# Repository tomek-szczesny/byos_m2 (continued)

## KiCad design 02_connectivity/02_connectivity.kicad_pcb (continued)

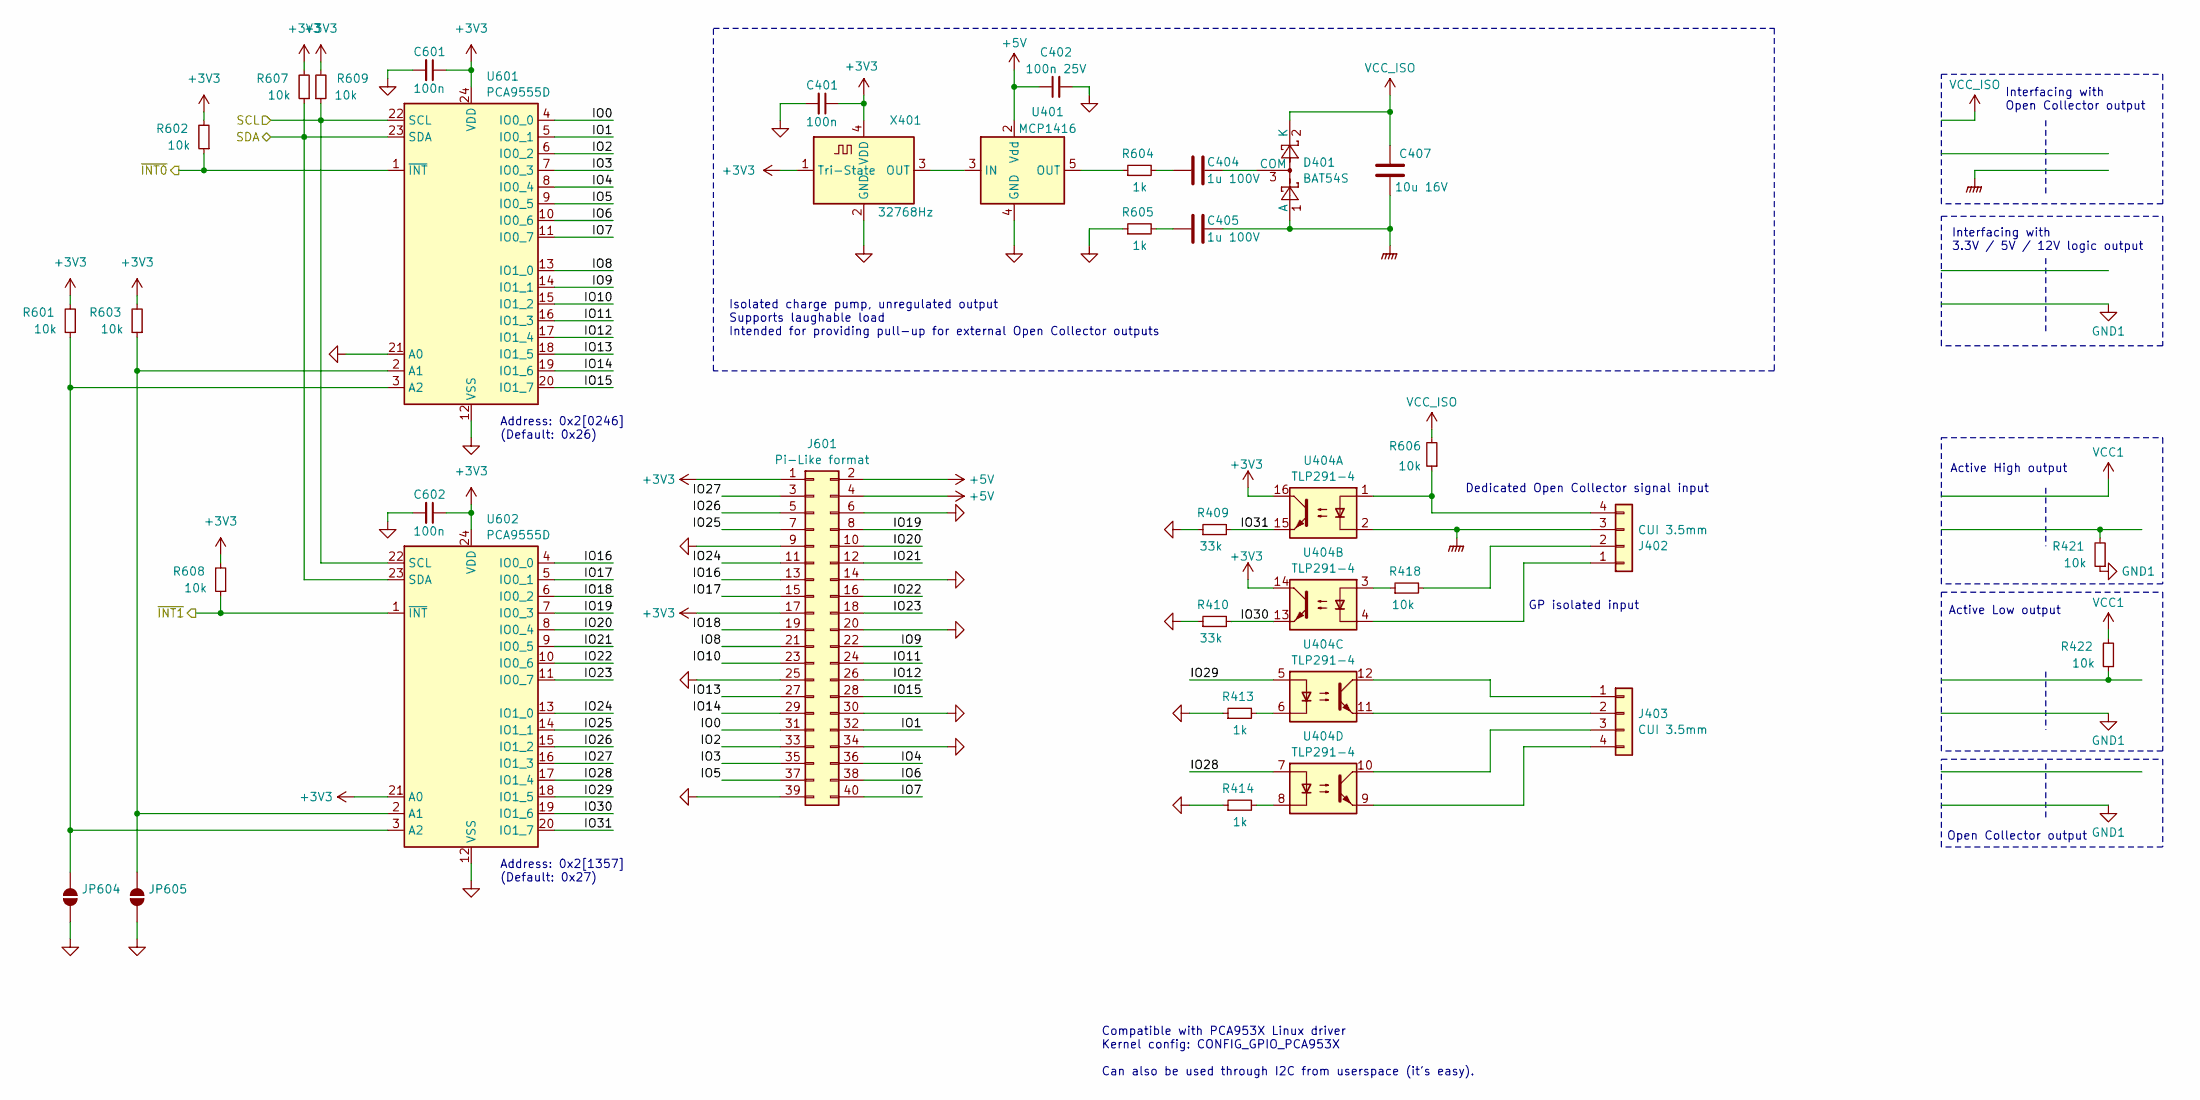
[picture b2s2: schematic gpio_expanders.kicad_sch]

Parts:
C401, C601, C602: 100n; C_0603_1608Metric
C402: 100n 25V; C_0603_1608Metric
C404, C405: 1u 100V; C_1206_3216Metric
C407: 10u 16V; C_1206_3216Metric
D401: BAT54S; SOT-23
J402, J403: CUI 3.5mm; CUI_TBP03R1-350-04BE
J601: Pi-Like format; PinHeader_2x20_P2.54mm_Horizontal
JP604, JP605: SolderJumper_2_Open; SolderJumper-2_P1.3mm_Open_TrianglePad1.0x1.5mm
R409, R410: 33k; R_0603_1608Metric
R413, R414, R604, R605: 1k; R_0603_1608Metric
R418, R421, R422, R601, R602, R603, R606, R607, R608, R609: 10k; R_0603_1608Metric
U401: MCP1416; SOT-23-5
U404: TLP291-4; SOIC-16_4.55x10.3mm_P1.27mm
U601, U602: PCA9555D; SOIC-24W_7.5x15.4mm_P1.27mm
X401: ECS-327MVATX-5-CN-TR; Oscillator_SMD_EuroQuartz_XO53-4Pin_5.0x3.2mm

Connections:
+3V3: C401.1, C601.1, C602.1, J601.1, J601.17, R601.2, R602.2, R603.2, R607.2, R608.2, R609.2, U404.14, U404.16, U601.24 (VDD), U602.21 (A0), U602.24 (VDD), X401.1 (Tri-State), X401.4 (VDD); also elsewhere on the board
+5V: C402.1, J601.2, J601.4, U401.2 (Vdd); also elsewhere on the board
/GPIO1_B2: R608.1, U602.1 (~INT); also elsewhere on the board
/GPIO1_B3: R602.1, U601.1 (~INT); also elsewhere on the board
/GPIO Expanders/IO0: J601.31, U601.4 (IO0_0)
/GPIO Expanders/IO1: J601.32, U601.5 (IO0_1)
/GPIO Expanders/IO2: J601.33, U601.6 (IO0_2)
/GPIO Expanders/IO3: J601.35, U601.7 (IO0_3)
/GPIO Expanders/IO4: J601.36, U601.8 (IO0_4)
/GPIO Expanders/IO5: J601.37, U601.9 (IO0_5)
/GPIO Expanders/IO6: J601.38, U601.10 (IO0_6)
/GPIO Expanders/IO7: J601.40, U601.11 (IO0_7)
/GPIO Expanders/IO8: J601.21, U601.13 (IO1_0)
/GPIO Expanders/IO9: J601.22, U601.14 (IO1_1)
/GPIO Expanders/IO10: J601.23, U601.15 (IO1_2)
/GPIO Expanders/IO11: J601.24, U601.16 (IO1_3)
/GPIO Expanders/IO12: J601.26, U601.17 (IO1_4)
/GPIO Expanders/IO13: J601.27, U601.18 (IO1_5)
/GPIO Expanders/IO14: J601.29, U601.19 (IO1_6)
/GPIO Expanders/IO15: J601.28, U601.20 (IO1_7)
/GPIO Expanders/IO16: J601.13, U602.4 (IO0_0)
/GPIO Expanders/IO17: J601.15, U602.5 (IO0_1)
/GPIO Expanders/IO18: J601.19, U602.6 (IO0_2)
/GPIO Expanders/IO19: J601.8, U602.7 (IO0_3)
/GPIO Expanders/IO20: J601.10, U602.8 (IO0_4)
/GPIO Expanders/IO21: J601.12, U602.9 (IO0_5)
/GPIO Expanders/IO22: J601.16, U602.10 (IO0_6)
/GPIO Expanders/IO23: J601.18, U602.11 (IO0_7)
/GPIO Expanders/IO24: J601.11, U602.13 (IO1_0)
/GPIO Expanders/IO25: J601.7, U602.14 (IO1_1)
/GPIO Expanders/IO26: J601.5, U602.15 (IO1_2)
/GPIO Expanders/IO27: J601.3, U602.16 (IO1_3)
/GPIO Expanders/IO28: U404.7, U602.17 (IO1_4)
/GPIO Expanders/IO29: U404.5, U602.18 (IO1_5)
/GPIO Expanders/IO30: R410.2, U404.13, U602.19 (IO1_6)
/GPIO Expanders/IO31: R409.2, U404.15, U602.20 (IO1_7)
/I2C6_SCL: R609.1, U601.22 (SCL), U602.22 (SCL); also elsewhere on the board
/I2C6_SDA: R607.1, U601.23 (SDA), U602.23 (SDA); also elsewhere on the board
GND: C401.2, C402.2, C601.2, C602.2, J601.6, J601.9, J601.14, J601.20, J601.25, J601.30, J601.34, J601.39, JP604.2 (B), JP605.2 (B), R409.1, R410.1, R413.1, R414.1, R605.1, U401.4 (GND), U601.12 (VSS), U601.21 (A0), U602.12 (VSS), X401.2 (GND); also elsewhere on the board
GND_ISO: C405.1, C407.1, D401.1 (A), J402.3, U404.2
unnamed: C404.2, R604.2
unnamed: C405.2, R605.2
unnamed: C404.1, D401.3 (COM)
unnamed: J402.1, U404.4
unnamed: J402.2, R418.2
unnamed: J402.4, R606.1, U404.1
unnamed: J403.1, U404.12
unnamed: J403.2, U404.11
unnamed: J403.3, U404.10
unnamed: J403.4, U404.9
unnamed: JP604.1 (A), R601.1, U601.3 (A2), U602.3 (A2)
unnamed: JP605.1 (A), R603.1, U601.2 (A1), U602.2 (A1)
unnamed: R413.2, U404.6
unnamed: R414.2, U404.8
unnamed: R418.1, U404.3
unnamed: U401.3 (IN), X401.3 (OUT)
unnamed: R604.1, U401.5 (OUT)
VCC_ISO: C407.2, D401.2 (K), R606.2

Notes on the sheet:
Isolated charge pump, unregulated output Supports laughable load Intended for providing pull-up for external Open Collector outputs
Active High output
Open Collector output
Dedicated Open Collector signal input
Active Low output
Interfacing with Open Collector output
Address: 0x2[1357] (Default: 0x27)
Interfacing with 3.3V / 5V / 12V logic output
GP isolated input
Compatible with PCA953X Linux driver Kernel config: CONFIG_GPIO_PCA953X Can also be used through I2C from userspace (it's easy).
Address: 0x2[0246] (Default: 0x26)

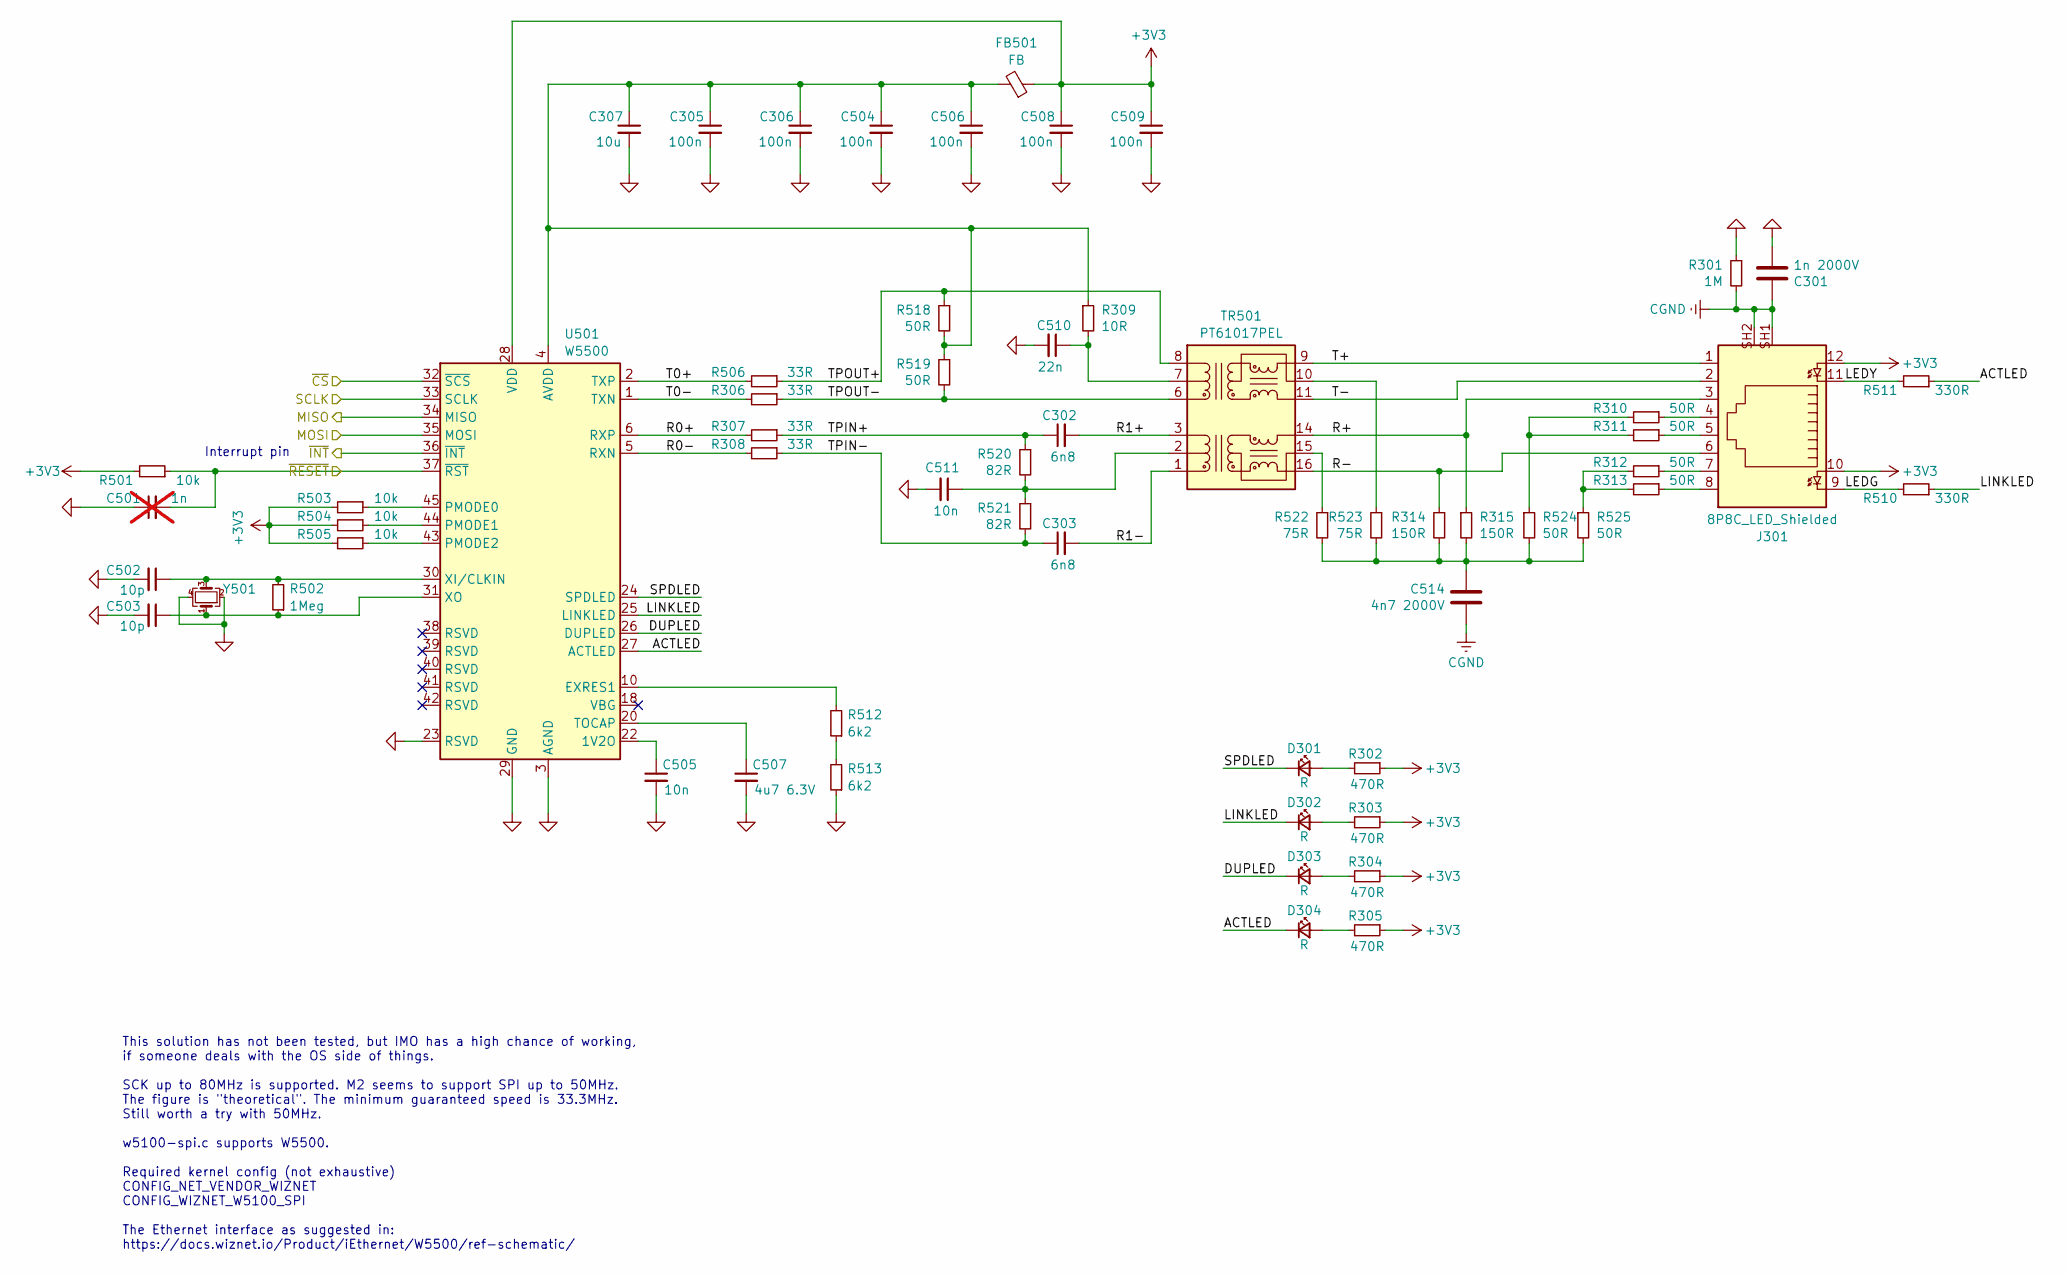
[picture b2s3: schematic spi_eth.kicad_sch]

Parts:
C301: 1n 2000V; C_1206_3216Metric
C302, C303: 6n8; C_0603_1608Metric
C305, C306, C504, C506, C508, C509: 100n; C_0603_1608Metric
C307: 10u; C_0603_1608Metric
C501: 1n; C_0603_1608Metric; not fitted
C502, C503: 10p; C_0603_1608Metric
C505, C511: 10n; C_0603_1608Metric
C507: 4u7 6.3V; C_0603_1608Metric
C510: 22n; C_0603_1608Metric
C514: 4n7 2000V; C_1206_3216Metric
D301, D302, D303, D304: R; LED_0603_1608Metric
FB501: FB; L_0603_1608Metric
J301: 8P8C_LED_Shielded; PHOENIX_1149867
R301: 1M; R_0603_1608Metric
R302, R303, R304, R305: 470R; R_0603_1608Metric
R306, R307, R308, R506: 33R; R_0603_1608Metric
R309: 10R; R_0603_1608Metric
R310, R311, R312, R313, R518, R519, R524, R525: 50R; R_0603_1608Metric
R314, R315: 150R; R_0603_1608Metric
R501, R503, R504, R505: 10k; R_0603_1608Metric
R502: 1Meg; R_0603_1608Metric
R510, R511: 330R; R_0603_1608Metric
R512, R513: 6k2; R_0603_1608Metric
R520, R521: 82R; R_0603_1608Metric
R522, R523: 75R; R_0603_1608Metric
TR501: PT61017PEL; Transformer_Ethernet_Bourns_PT61017PEL
U501: W5500; LQFP-48_7x7mm_P0.5mm
Y501: ABM8-25.000MHZ-B2-T; Crystal_SMD_3225-4Pin_3.2x2.5mm

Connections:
+3V3: C508.1, C509.1, FB501.1, J301.10, J301.12, R302.1, R303.1, R304.1, R305.1, R501.2, R503.2, R504.2, R505.2, U501.28 (VDD); also elsewhere on the board
/GPIO3_D5: U501.36 (~INT); also elsewhere on the board
/GPIO4_B3: C501.2, R501.1, U501.37 (~RST); also elsewhere on the board
/SPI3_CS0: U501.32 (~SCS); also elsewhere on the board
/SPI3_MISO: U501.34 (MISO); also elsewhere on the board
/SPI3_MOSI: U501.35 (MOSI); also elsewhere on the board
/SPI3_SCK: U501.33 (SCLK); also elsewhere on the board
/SPI Ethernet/ACTLED: D304.1 (K), R511.1, U501.27 (ACTLED)
/SPI Ethernet/DUPLED: D303.1 (K), U501.26 (DUPLED)
/SPI Ethernet/LEDG: J301.9, R510.2
/SPI Ethernet/LEDY: J301.11, R511.2
/SPI Ethernet/LINKLED: D302.1 (K), R510.1, U501.25 (LINKLED)
/SPI Ethernet/R0+: R307.2, U501.6 (RXP)
/SPI Ethernet/R0-: R308.2, U501.5 (RXN)
/SPI Ethernet/R1+: C302.2, TR501.3 (TD-)
/SPI Ethernet/R1-: C303.2, TR501.1 (TD+)
/SPI Ethernet/R+: J301.3, R315.1, TR501.14 (TX-)
/SPI Ethernet/R-: J301.6, R314.1, TR501.16 (TX+)
/SPI Ethernet/SPDLED: D301.1 (K), U501.24 (SPDLED)
/SPI Ethernet/T0+: R506.2, U501.2 (TXP)
/SPI Ethernet/T0-: R306.2, U501.1 (TXN)
/SPI Ethernet/T+: J301.1, TR501.9 (RX-)
/SPI Ethernet/T-: J301.2, TR501.11 (RX+)
/SPI Ethernet/TPIN+: C302.1, R307.1, R520.1
/SPI Ethernet/TPIN-: C303.1, R308.1, R521.2
/SPI Ethernet/TPOUT+: R506.1, R518.1, TR501.8 (RD-)
/SPI Ethernet/TPOUT-: R306.1, R519.2, TR501.6 (RD+)
CGND: C301.1, C514.2, J301.SH1, J301.SH2, R301.2
GND: C301.2, C305.2, C306.2, C307.2, C501.1, C502.2, C503.2, C504.2, C505.2, C506.2, C507.2, C508.2, C509.2, C510.2, C511.2, R301.1, R513.1, U501.3 (AGND), U501.9 (AGND), U501.14 (AGND), U501.16 (AGND), U501.19 (AGND), U501.23 (RSVD), U501.29 (GND), U501.48 (AGND), Y501.2, Y501.4; also elsewhere on the board
unnamed: C305.1, C306.1, C307.1, C504.1, C506.1, FB501.2, R309.1, R518.2, R519.1, U501.4 (AVDD), U501.8 (AVDD), U501.11 (AVDD), U501.15 (AVDD), U501.17 (AVDD), U501.21 (AVDD)
unnamed: C514.1, R314.2, R315.2, R522.2, R523.2, R524.2, R525.2
unnamed: D301.2 (A), R302.2
unnamed: D302.2 (A), R303.2
unnamed: D303.2 (A), R304.2
unnamed: D304.2 (A), R305.2
unnamed: J301.4, R310.1
unnamed: J301.5, R311.1
unnamed: J301.7, R312.1
unnamed: J301.8, R313.1
unnamed: R310.2, R311.2, R524.1
unnamed: R312.2, R313.2, R525.1
unnamed: R512.1, R513.2
unnamed: C510.1, R309.2, TR501.7 (C_RD)
unnamed: R523.1, TR501.10 (C_RX)
unnamed: C511.1, R520.2, R521.1, TR501.2 (C_TD)
unnamed: R522.1, TR501.15 (C_TX)
unnamed: C505.1, U501.22 (1V2O)
unnamed: R512.2, U501.10 (EXRES1)
unnamed: R503.1, U501.45 (PMODE0)
unnamed: R504.1, U501.44 (PMODE1)
unnamed: R505.1, U501.43 (PMODE2)
unnamed: C507.1, U501.20 (TOCAP)
unnamed: C502.1, R502.2, U501.30 (XI/CLKIN), Y501.3
unnamed: C503.1, R502.1, U501.31 (XO), Y501.1

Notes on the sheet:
This solution has not been tested, but IMO has a high chance of working, if someone deals with the OS side of things. SCK up to 80MHz is supported. M2 seems to support SPI up to 50MHz. The figure is "theoretical". The minimum guaranteed speed is 33.3MHz. Still worth a try with 50MHz. w5100-spi.c su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
Interrupt pin

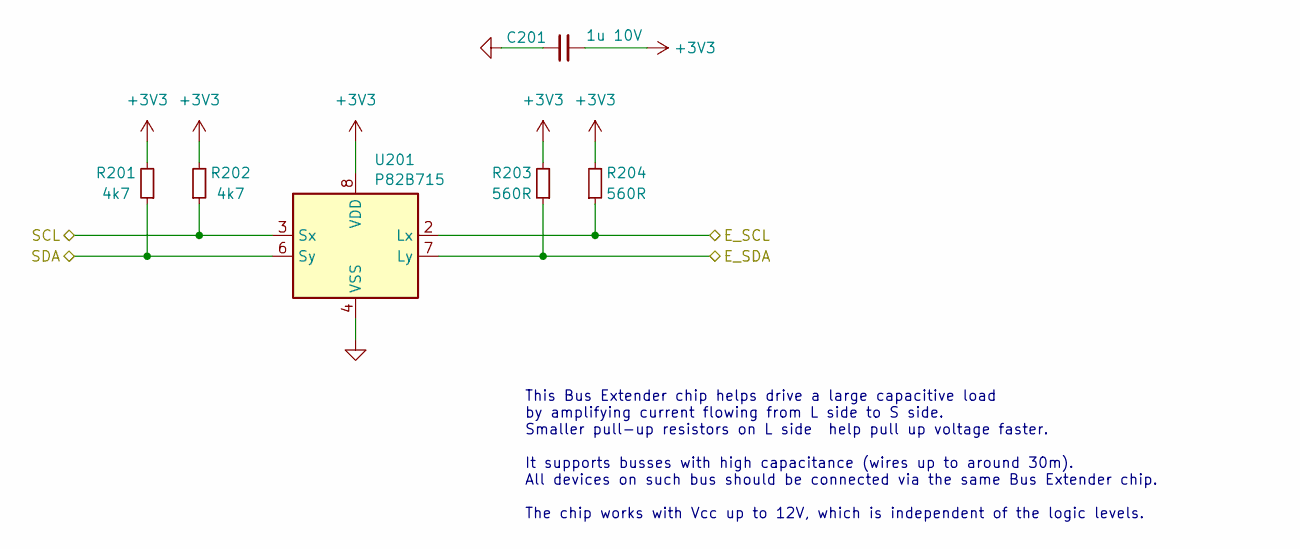
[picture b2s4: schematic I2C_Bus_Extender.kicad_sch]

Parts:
C201: 1u 10V; C_0603_1608Metric
R201, R202: 4k7; R_0603_1608Metric
R203, R204: 560R; R_0603_1608Metric
U201: P82B715; SOIC-8_3.9x4.9mm_P1.27mm

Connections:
+3V3: C201.2, R201.2, R202.2, R203.2, R204.2, U201.8 (VDD); also elsewhere on the board
/I2C5_SCL: R202.1, U201.3 (Sx); also elsewhere on the board
/I2C5_SDA: R201.1, U201.6 (Sy); also elsewhere on the board
/I2C Bus Extender/E_SCL: R204.1, U201.2 (Lx); also elsewhere on the board
/I2C Bus Extender/E_SDA: R203.1, U201.7 (Ly); also elsewhere on the board
GND: C201.1, U201.4 (VSS); also elsewhere on the board

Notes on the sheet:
This Bus Extender chip helps drive a large capacitive load by amplifying current flowing from L side to S side. Smaller pull-up resistors on L side help pull up voltage faster. It supports busses with high capacitance (wires up to around 30m). All devices on such bus should be connected via the sam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

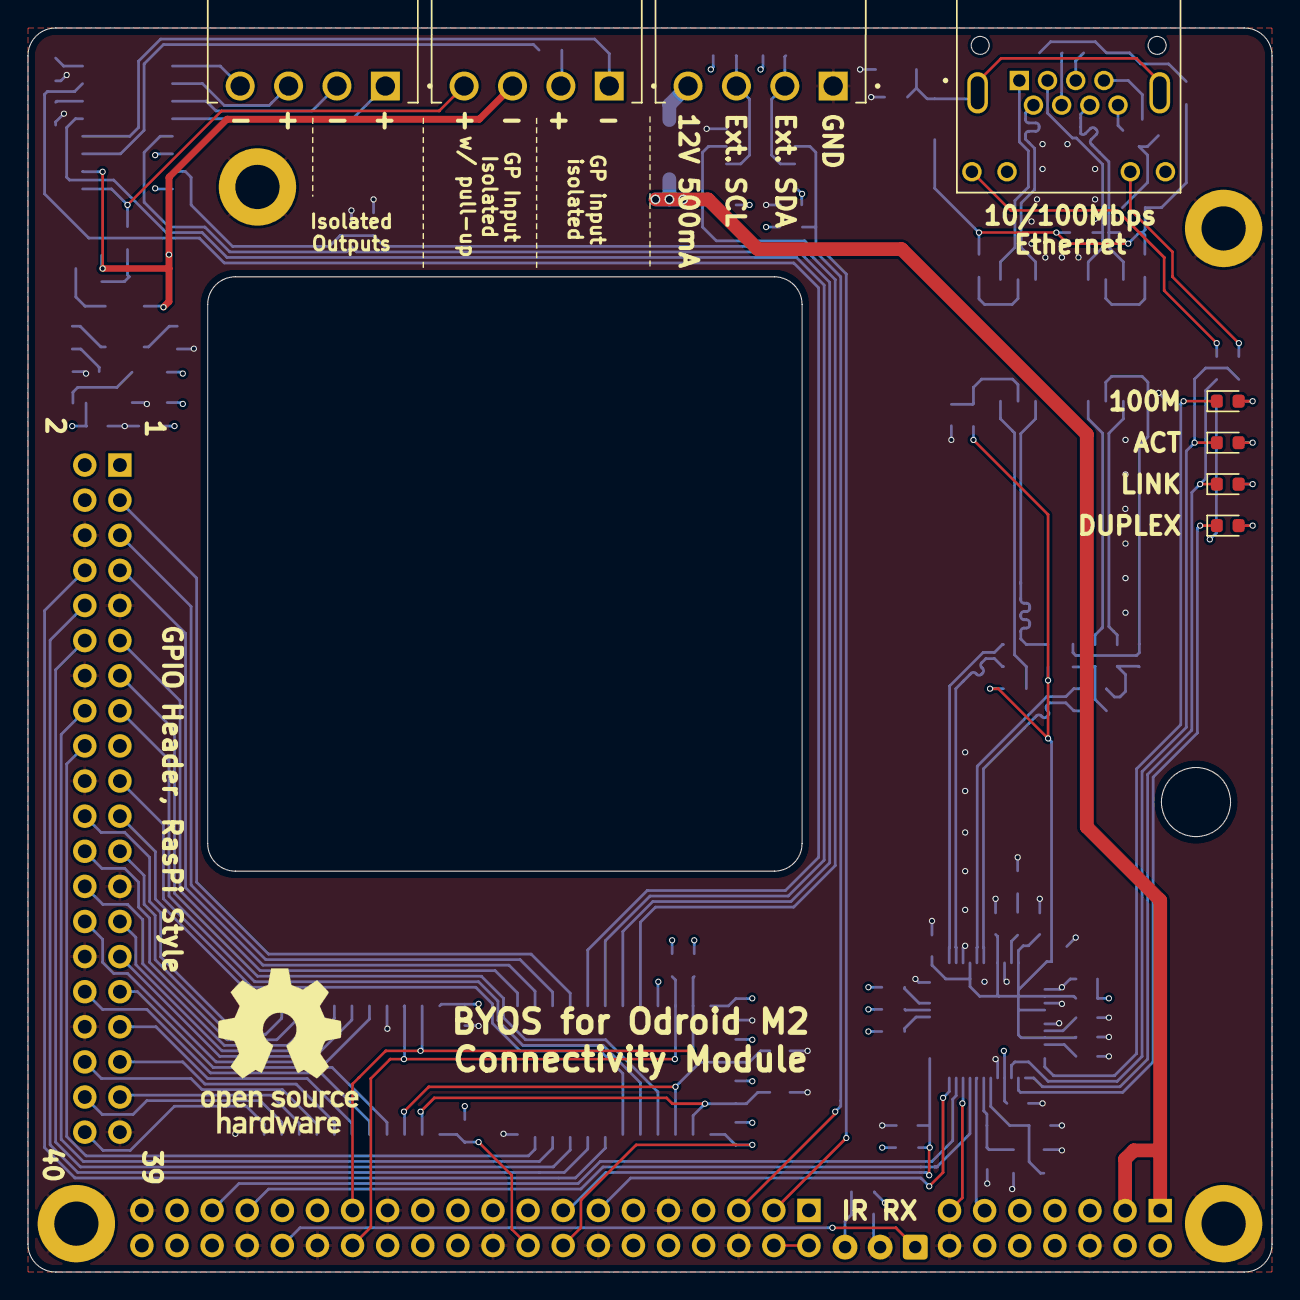
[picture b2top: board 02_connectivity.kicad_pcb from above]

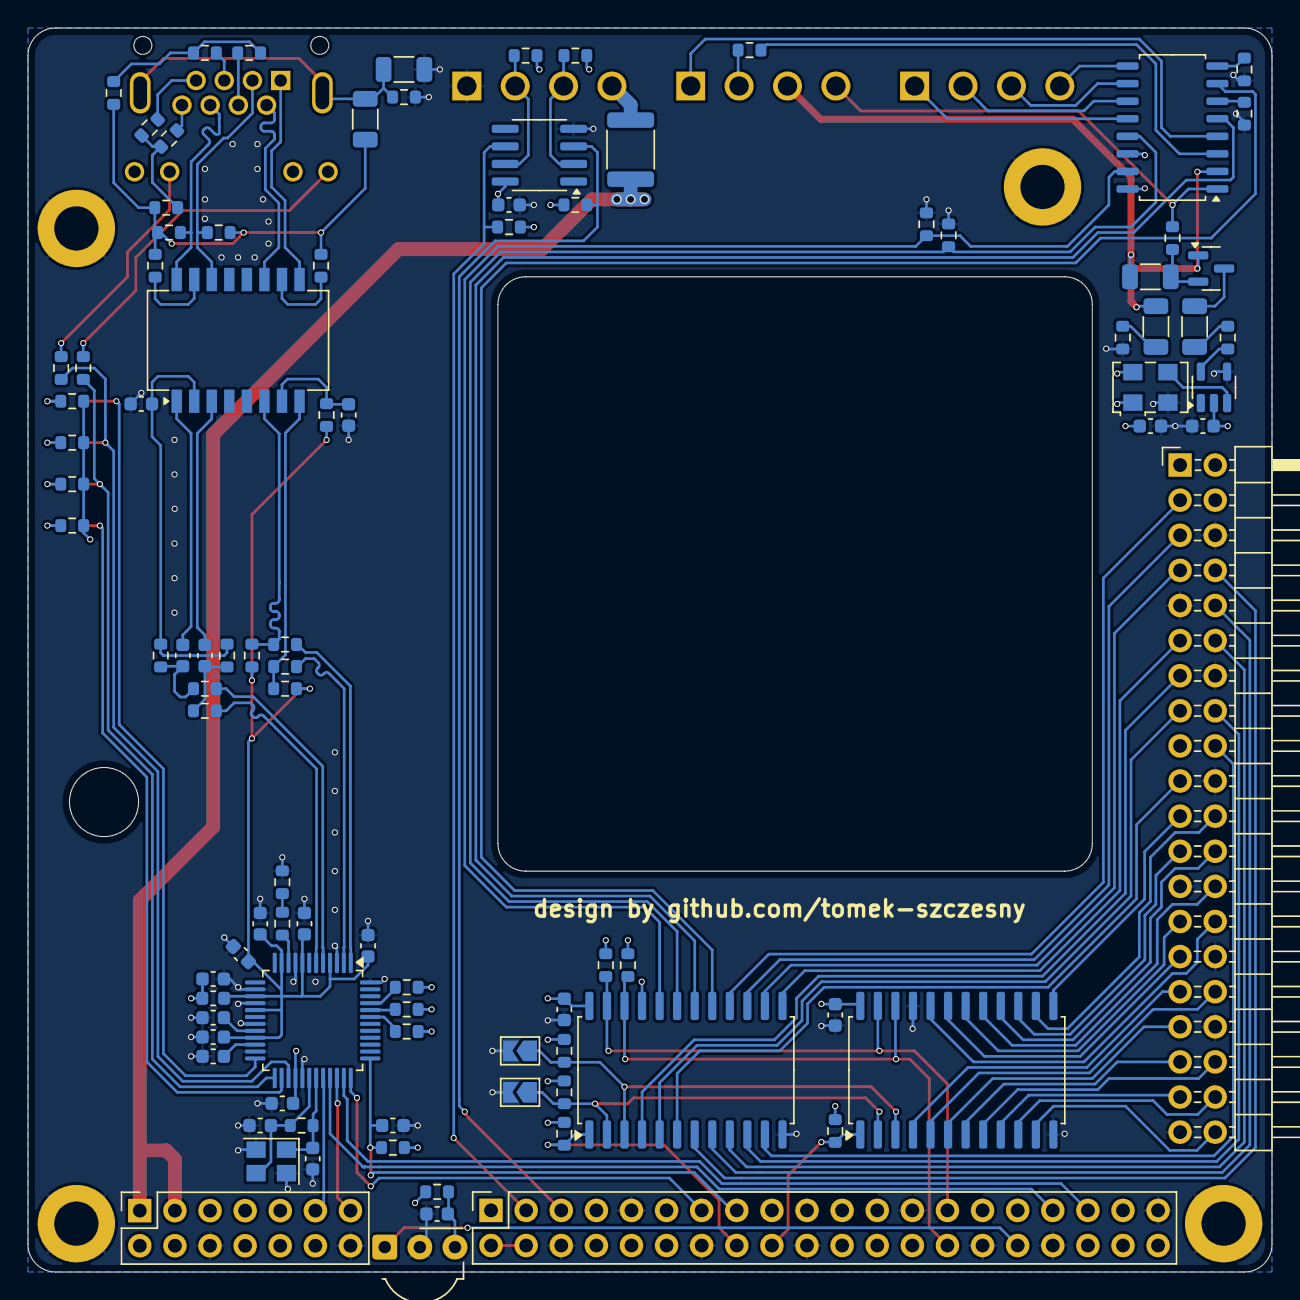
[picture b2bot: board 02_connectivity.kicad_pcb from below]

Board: 4 copper layers, 90.0 x 90.0 mm, 110 parts (97 on the bottom side), 118 nets.

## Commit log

2024-10-03 Initial commit of the audio amp
2024-10-11 Board #2: Connectivity Board
2024-10-16 Module no. 1 completely redesigned
